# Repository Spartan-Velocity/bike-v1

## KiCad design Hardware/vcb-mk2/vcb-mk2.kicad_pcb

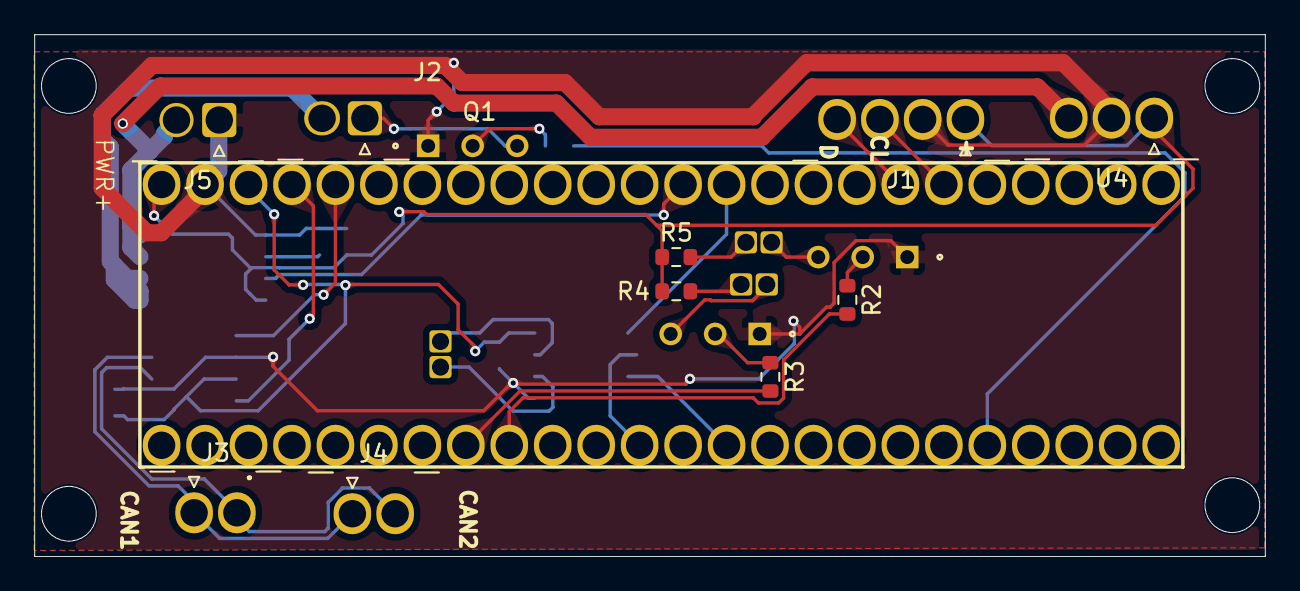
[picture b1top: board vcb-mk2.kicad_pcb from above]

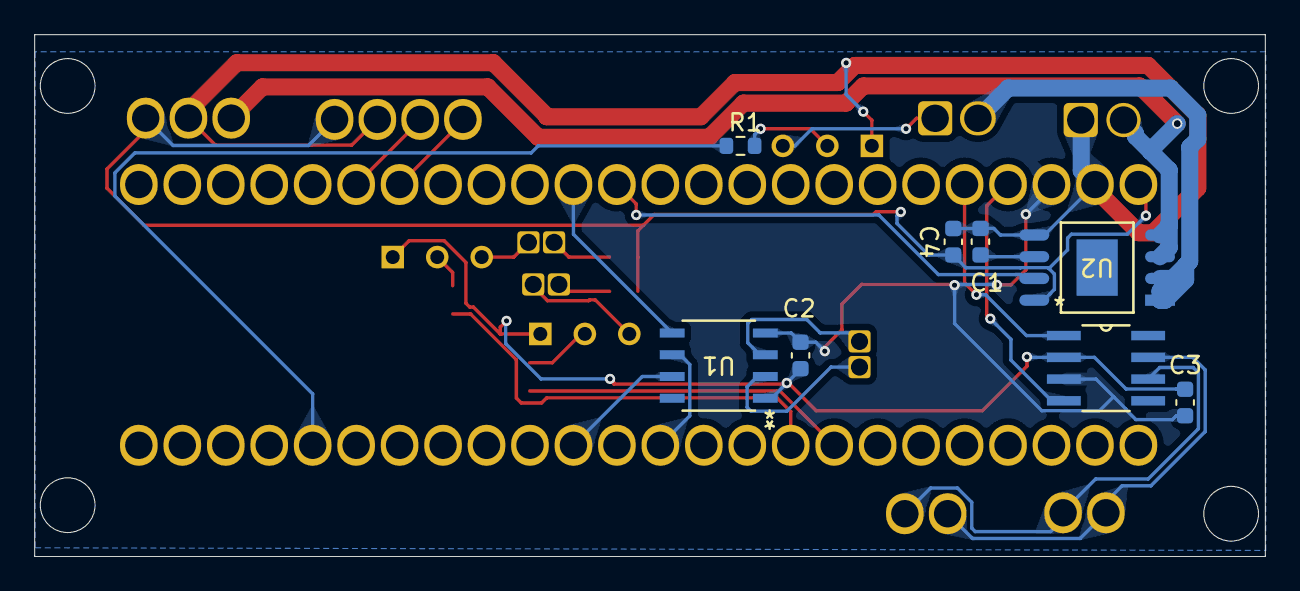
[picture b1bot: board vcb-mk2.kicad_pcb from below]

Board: 2 copper layers, 71.9 x 30.5 mm, 22 parts (8 on the bottom side), 23 nets.

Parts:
C1, C3: 1nF; C_0603_1608Metric
C2, C4: 0.1uF; C_0603_1608Metric
IC1: TEENSY_4.1; TEENSY41
J1: Conn_01x04; JST_XH_S4B-XH-A_1x04_P2.50mm_Horizontal
J2, J3, J4, J5: Conn_01x02; JST_XH_S2B-XH-A_1x02_P2.50mm_Horizontal
Q1, Q1#2, Q1#3: 2N2222; TO-92-3L_5P33X5P2_ONS
R1, R2, R3: 1k; R_0603_1608Metric
R4: 100; R_0603_1608Metric
R5: 150; R_0603_1608Metric
U1: MAX31855KASA+T; 21-0041B_8_MXM
U2: ACS712xLCTR-05B; SOIC-8_ALM
U4: Pololu_D24v50f5; JST_XH_S3B-XH-A_1x03_P2.50mm_Horizontal
U5: SN65HVD230D; D8

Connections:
+3.3v: C2.2, C3.2, IC1.53 (3.3V_(250_M_A_MAX)), U1.4 (VCC), U5.3 (VCC)
+5v: C4.1, IC1.55 (VIN_(3.6_TO_5.5_VOLTS)), J1.1, R4.1, R5.1, U2.8 (VCC), U4.1 (Vout)
+12v: J5.2, U2.3 (IP-), U2.4 (IP-), U4.3 (Vin)
CAN+: J3.1, J4.1, U5.7 (CANH)
CAN-: J3.2, J4.2, U5.6 (CANL)
CRX: IC1.23 (A9), U5.4 (R)
CTX: IC1.22 (A8), U5.1 (D)
D6: IC1.6 (OUT1D), R3.2
D7: IC1.7 (RX2), R2.2
FILTER: C1.2, U2.6 (FILTER)
GND: C1.1, C2.1, C3.1, C4.2, IC1.70 (GND_5), J1.2, J5.1, Q1.1 (E), Q1#2.1 (E), Q1#3.1 (E), U1.1 (GND), U2.5 (GND), U4.2 (GND), U5.2 (GND)
unnamed: Q1#2.2 (B), R1.1
unnamed: Q1.2 (B), R3.1
unnamed: Q1#3.2 (B), R2.1
PUMP_PWM: J2.1, Q1#2.3 (C)
PWM: IC1.28 (RX7), R1.2
Pump: J2.2, U2.1 (IP+), U2.2 (IP+)
SCK: IC1.13 (SCK), U1.5 (SCK)
SCL: IC1.38 (A14), J1.3
SDA: IC1.39 (A15), J1.4
SO: IC1.12 (MISO), U1.7 (SO)
TEMP_CS: IC1.10 (CS_1), U1.6 (*CS)
VIOUT: IC1.14 (A0), U2.7 (VIOUT)
